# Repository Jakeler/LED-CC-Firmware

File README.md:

# Constant current LED Driver

Microcontroller based constant current driver. Based around a LM2596S drop down regulator (because these complete modules are cheaper than buying the components) and an Arduino Pro Mini.

The repo contains a PlatformIO project to compile the Arduino firmware. In the schematic/ subdirectory is the KiCAD project with the PCB layout, footprints, etc.

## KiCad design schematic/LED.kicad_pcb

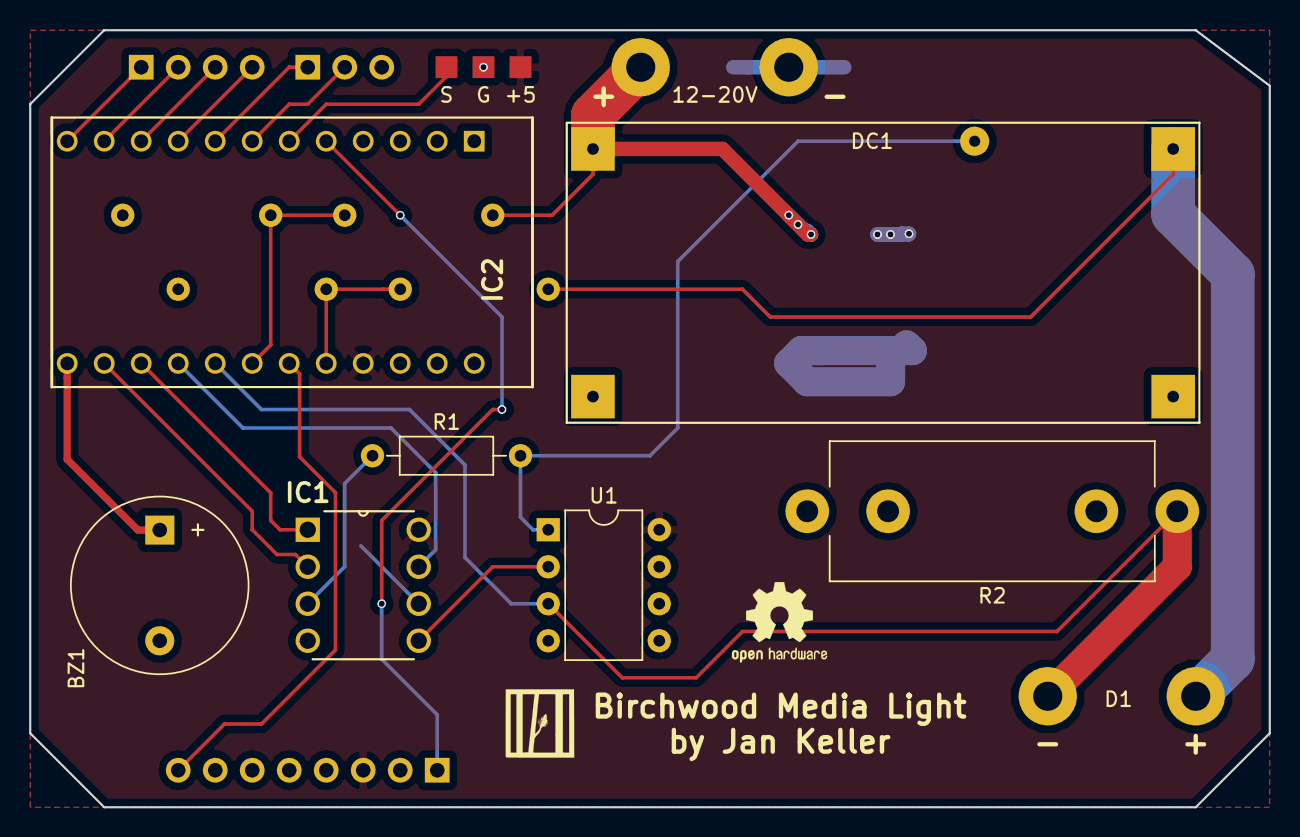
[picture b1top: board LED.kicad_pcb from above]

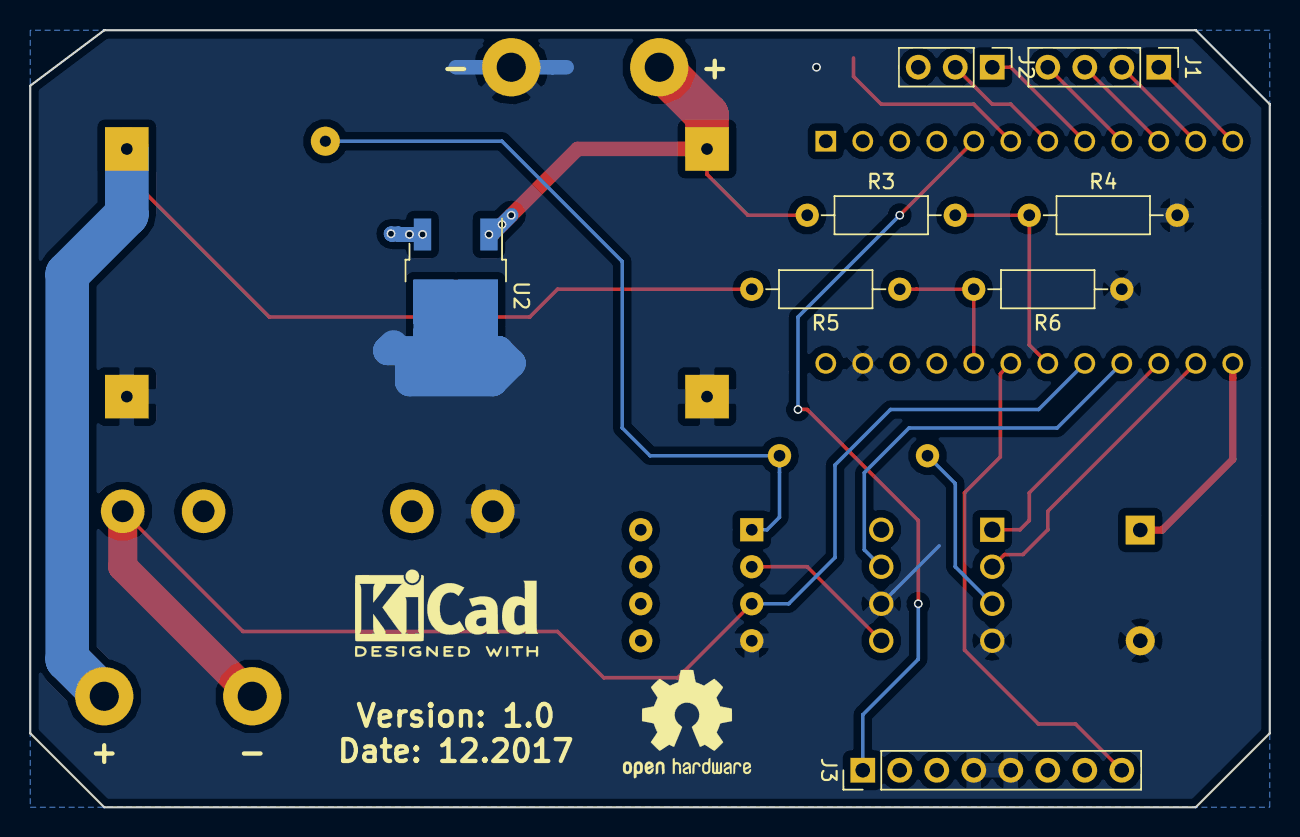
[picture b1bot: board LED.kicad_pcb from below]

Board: 2 copper layers, 85.1 x 53.3 mm, 20 parts (8 on the bottom side), 23 nets.

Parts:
12-20V: 3-4S LiPo; WireConnection_2.00mmDrill
+5: Measurement_Point_Square-SMD-Pad_Small
BZ1: Buzzer; Buzzer_12x9.5RM7.6
D1: LED; WireConnection_2.00mmDrill
DC1: DC-DC; ChinaLM2596S-Module
G: Measurement_Point_Square-SMD-Pad_Small
IC1: X9C103P; DIP254P762X533-8
IC2: Pro Mini; ProMini
J1: Conn_01x04; Socket_Strip_Straight_1x04_Pitch2.54mm
J2: Conn_01x03; Socket_Strip_Straight_1x03_Pitch2.54mm
J3: Conn_01x06; Socket_Strip_Straight_1x08_Pitch2.54mm
R1: 20K; R_Axial_DIN0207_L6.3mm_D2.5mm_P10.16mm_Horizontal
R2: 0.39; R_Axial_Shunt_L22.2mm_W9.5mm_PS14.30mm_P25.40mm
R3, R5: 15K; R_Axial_DIN0207_L6.3mm_D2.5mm_P10.16mm_Horizontal
R4, R6: 4.7K; R_Axial_DIN0207_L6.3mm_D2.5mm_P10.16mm_Horizontal
S: Measurement_Point_Square-SMD-Pad_Small
U1: LM358; DIP-8_W7.62mm
U2: MC78M05_TO252; TO-252-2

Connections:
+5V: +5.1, IC1.8, IC2.21, J3.3, U1.8, U2.3
+BATT: 12-20V.1, DC1.1, R3.1, U2.1
GND: 12-20V.2, BZ1.2, DC1.2, DC1.4, G.1, IC1.4, IC1.6, IC2.23, J3.4, J3.5, R2.4, R4.2, R6.1, U1.4, U2.2
unnamed: BZ1.1, IC2.13
unnamed: D1.1, IC2.17, R2.1, U1.3
unnamed: D1.2, DC1.5, R5.2
unnamed: DC1.3, R1.2, U1.1
unnamed: IC1.1, IC2.15
unnamed: IC1.2, IC2.14
unnamed: IC1.3, R1.1
unnamed: IC1.5, U1.2
unnamed: IC1.7, IC2.16
unnamed: IC2.5, J3.1
unnamed: IC2.6, S.1
unnamed: IC2.7, J2.2
unnamed: IC2.8, J2.1
unnamed: IC2.9, J1.4
unnamed: IC2.10, J1.3
unnamed: IC2.11, J1.2
unnamed: IC2.12, J1.1
unnamed: IC2.18, R3.2, R4.1
unnamed: IC2.19, J3.8
VS: IC2.20, R5.1, R6.2

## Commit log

2017-12-27 Import Prototype
2017-12-27 Add output voltage/current mesurment
2017-12-27 Disbale digital Pot when not used
2017-12-27 Add self test at startup and power display
2017-12-27 Fix Poti Standby
2017-12-27 Uncomment travis CI
2017-12-28 Create LICENSE
2018-08-01 Add KiCAD schematics
2018-08-01 Mention schematics in Readme
2018-08-01 Fix readme layout
2022-08-07 Update to platformio 6 libs
2022-08-07 Add more general constant current firmware
2022-08-07 Add enable/disable button function
2022-08-07 Rename `pot_pos` to `potiPos`
2022-08-07 Display wattage
2022-08-10 Use source filter for different variants also more stuff in common [env]
2022-08-13 Build libs for current and sensors
2022-08-13 Move target und powered global var into class
2022-08-14 Create button/beeper class lib
2022-08-15 Pin definitions as class member var
2022-08-15 Create PowerSensor class for volt/amp/watt reading
2022-08-17 Add tec controller env with DS18B20
2022-08-17 Improve temp display and clean up Serial
2022-08-22 Integrate QuickPID
2022-08-22 250 kbaud for serial monitor
